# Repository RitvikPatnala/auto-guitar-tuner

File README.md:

# Auto Guitar Tuner

A handheld device that detects a guitar string's pitch and physically rotates the tuning peg until the string is in tune. Built around a custom ESP32-S3 PCB designed from schematic capture to routed layout, with real-time pitch detection firmware and closed-loop servo control. Tunes to within ±12 cents across all six strings and multiple tuning standards (Standard, Eb, Drop D, Open G).

## How it works?

1. A piezo vibration sensor mounted on the guitar picks up string vibrations (immune to ambient room noise, unlike a microphone).
2. An LM386 amplifier stage (gain ≈ 50) with a 1.6 kHz RC anti-aliasing filter conditions the signal for the ESP32-S3's ADC (8192 Hz, 12-bit).
3. Firmware detects the fundamental frequency using time-domain autocorrelation and computes the error from the target pitch in cents.
4. A PID controller drives an HS-318 servo attached to the tuning peg, making small angular corrections until the string is in tune — with safety interlocks (rotation limits, stall           detection, voicing threshold) to protect the guitar.
5. A TFT LCD (SPI) and two-button interface let the user select strings and tuning modes via an FSM-driven UI.

## Why Autocorrelation instaead of FFT?

The most interesting design decision in the project. Guitar strings produce strong harmonics — the 2nd harmonic often carries more energy than the fundamental, so naive FFT peak-picking frequently reports the octave above the true pitch. Time-domain autocorrelation measures the signal's self-similarity across lag values, which naturally locks onto the fundamental period. It was also faster on the ESP32-S3:

| Approach | Latency |
|---|---|
| Autocorrelation | ~22 ms |
| FFT + peak detection | ~48 ms |

The pipeline: Hann window → autocorrelation over the guitar's lag range (73–330 Hz) → normalization → zero-crossing peak detection → parabolic sub-sample interpolation for resolution beyond the lag grid. The ~22 ms loop lets the tuner track pitch continuously while the motor turns, so the user doesn't need to re-pluck after every adjustment.

## Hardware Design

- Power: dual AP62150 buck converters (9V battery → 5V and 3.3V rails). Chosen over LDOs after a dissipation analysis — a stalled servo draws 800 mA, which would burn 3.2 W in an LDO vs ~90% buck efficiency.
- Custom PCB: designed in KiCAD (schematic → layout), simulated in LTSpice; noise mitigated with ground partitioning, supply decoupling, and the RC input filter.

- Motor: HS-318 analog servo, selected over a stepper for closed-loop position feedback and full torque at low speed. Torque analysis: 0.25 kg·cm required at the peg vs 3.7 kg·cm available.

## Verification Highlights

| Subsystem | Result |
|---|---|
| Power rails | 3.353 V / 4.995 V measured (±1% of nominal) |
| Audio chain | Gain of ~52 measured (target 50); piezo signal 84 mV |
| Pitch detection | ±12 cents final tuning accuracy, ~22 ms latency |
| Control | Autonomous tuning verified on all 6 strings + alternate tunings |

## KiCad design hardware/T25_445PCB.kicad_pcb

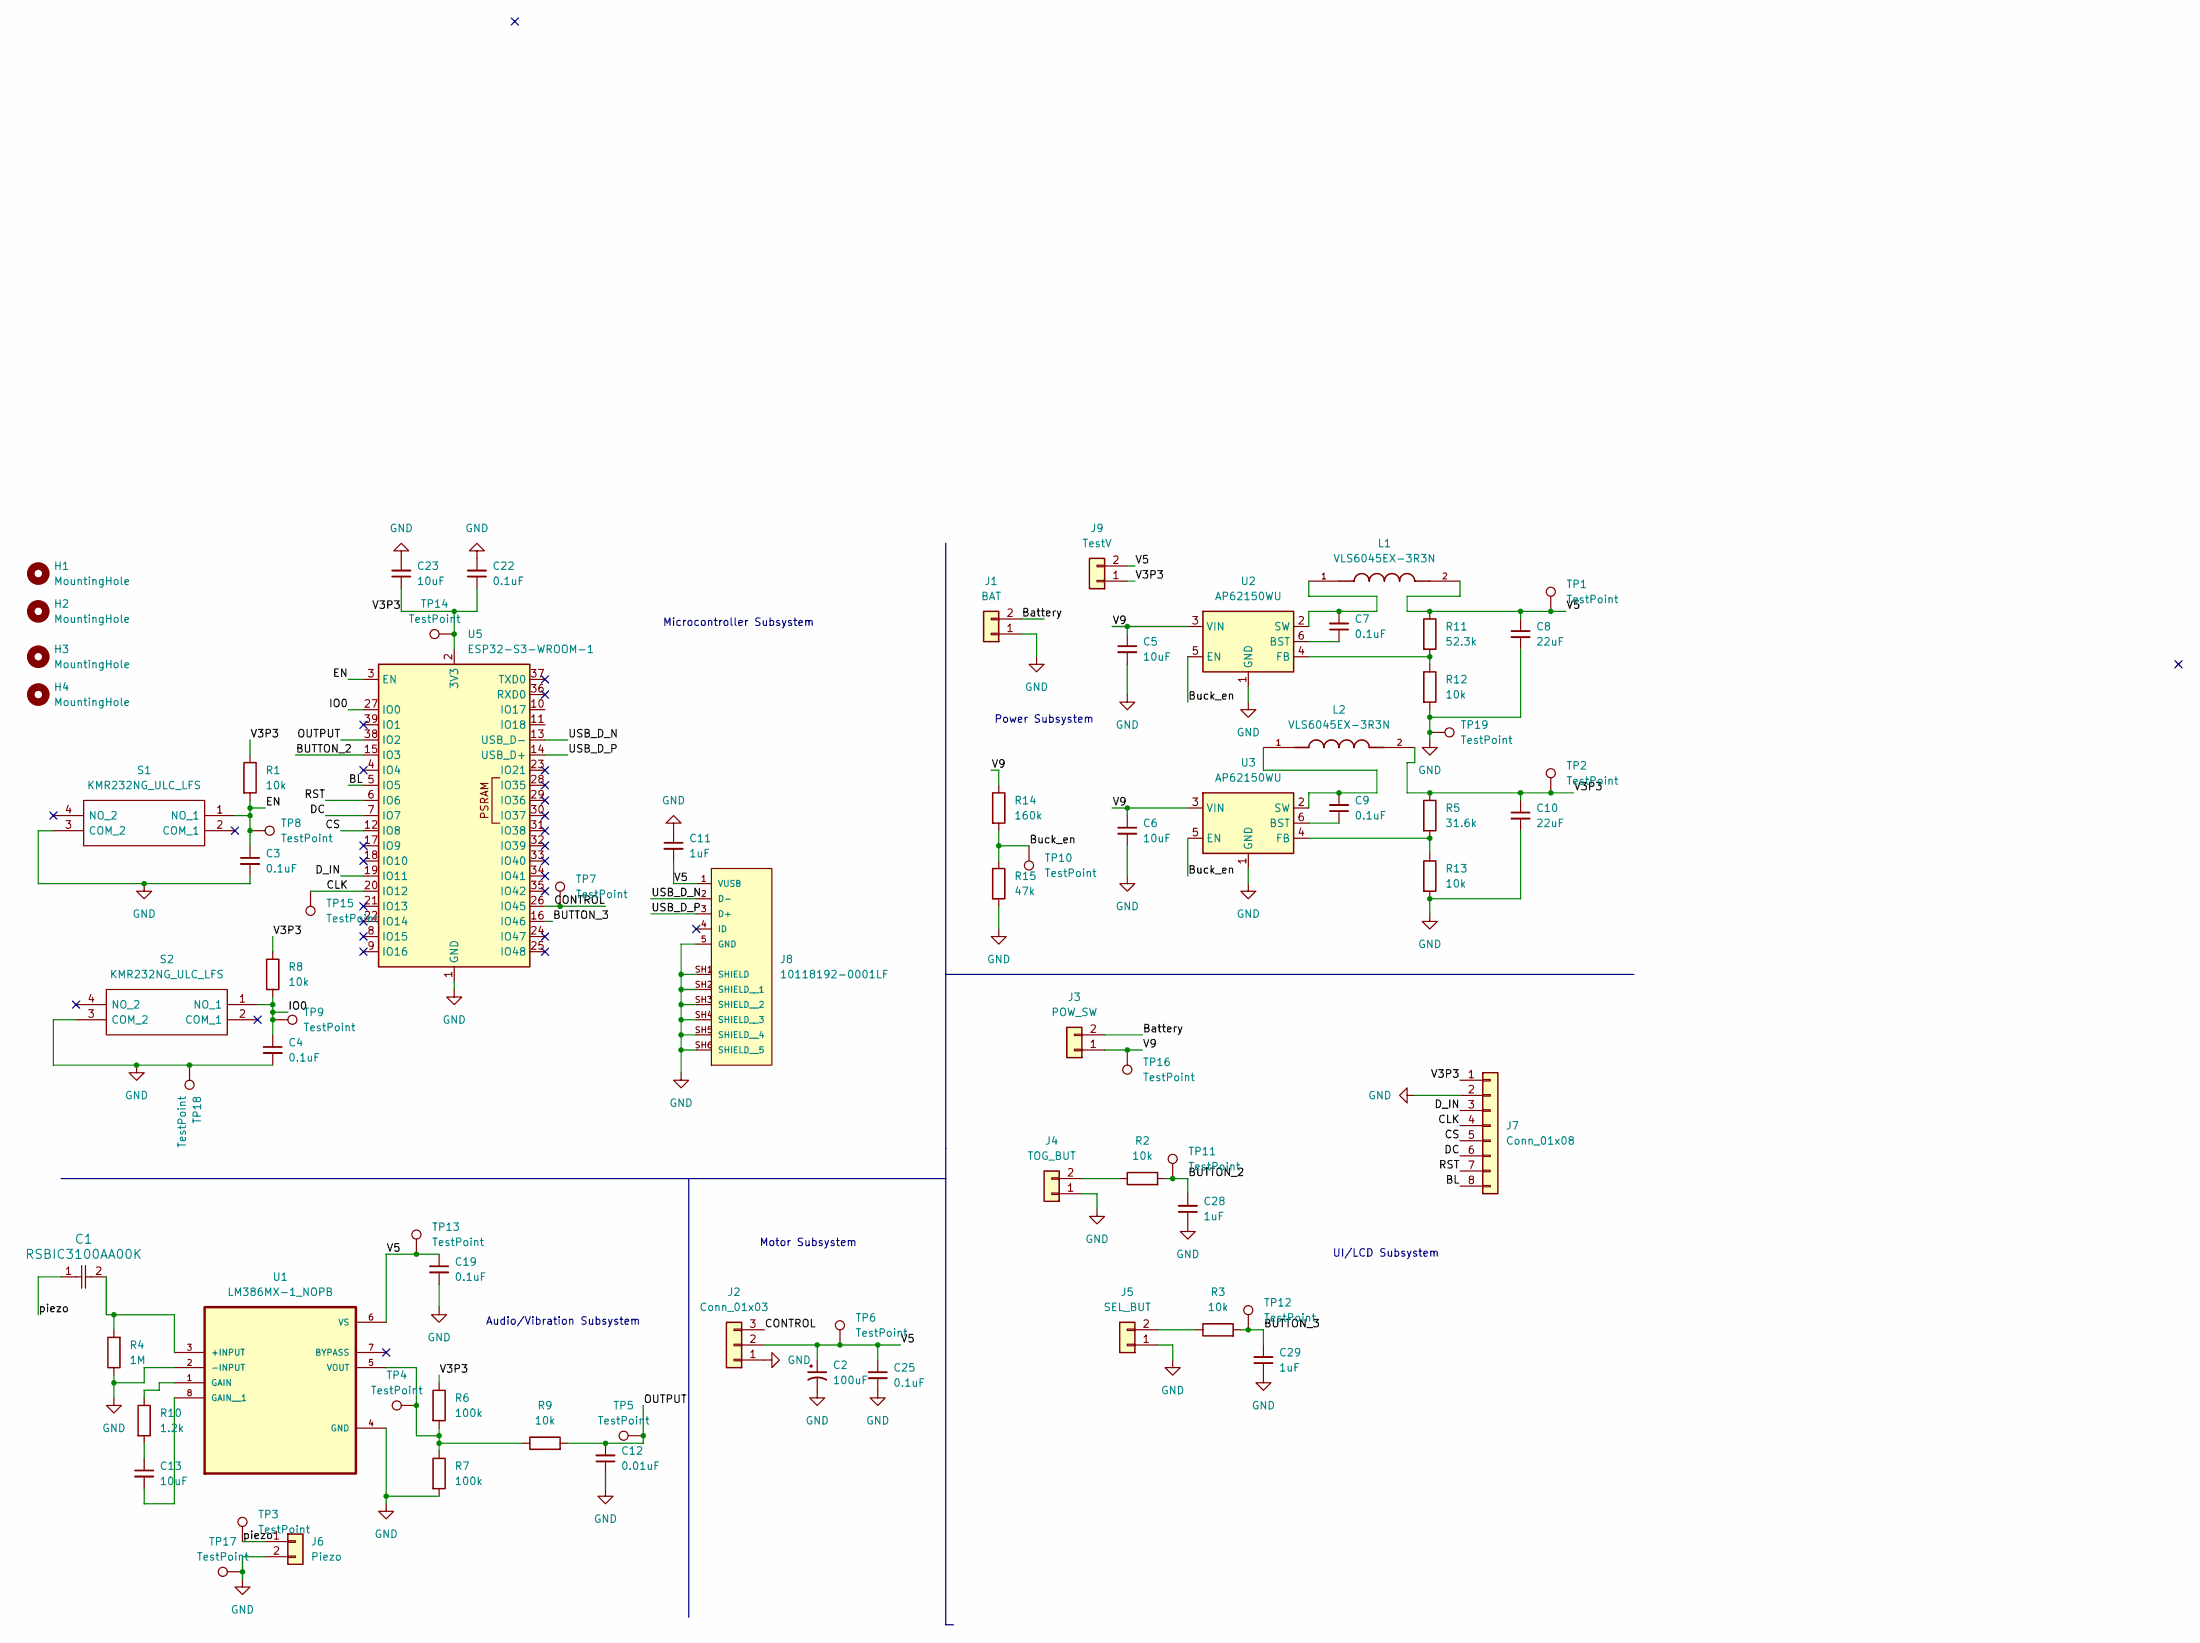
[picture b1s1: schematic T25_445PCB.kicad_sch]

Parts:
C1: RSBIC3100AA00K; CAP_RSBIC3100AA00K_KEM
C2: 100uF; CP_Radial_D6.3mm_P2.50mm
C3, C4, C7, C9, C19, C22, C25: 0.1uF; C_0805_2012Metric_Pad1.18x1.45mm_HandSolder
C5, C6, C13, C23: 10uF; C_0805_2012Metric_Pad1.18x1.45mm_HandSolder
C8, C10: 22uF; C_0805_2012Metric_Pad1.18x1.45mm_HandSolder
C11, C28, C29: 1uF; C_0805_2012Metric_Pad1.18x1.45mm_HandSolder
C12: 0.01uF; C_0805_2012Metric_Pad1.18x1.45mm_HandSolder
H1, H2, H3, H4: MountingHole; MountingHole_3.2mm_M3
J1: BAT; Molex_KK-254_AE-6410-02A_1x02_P2.54mm_Vertical
J2: Conn_01x03; Molex_KK-254_AE-6410-03A_1x03_P2.54mm_Vertical
J3: POW_SW; Molex_KK-254_AE-6410-02A_1x02_P2.54mm_Vertical
J4: TOG_BUT; Molex_KK-254_AE-6410-02A_1x02_P2.54mm_Vertical
J5: SEL_BUT; Molex_KK-254_AE-6410-02A_1x02_P2.54mm_Vertical
J6: Piezo; Molex_KK-254_AE-6410-02A_1x02_P2.54mm_Vertical
J7: Conn_01x08; Molex_KK-254_AE-6410-08A_1x08_P2.54mm_Vertical
J8: 10118192-0001LF; AMPHENOL_10118192-0001LF
J9: TestV; Molex_KK-254_AE-6410-02A_1x02_P2.54mm_Vertical
L1, L2: VLS6045EX-3R3N; IND_VLS6045EX-3R3N
R1, R2, R3, R8, R9, R12, R13: 10k; R_0805_2012Metric_Pad1.20x1.40mm_HandSolder
R4: 1M; R_0805_2012Metric_Pad1.20x1.40mm_HandSolder
R5: 31.6k; R_0805_2012Metric_Pad1.20x1.40mm_HandSolder
R6, R7: 100k; R_0805_2012Metric_Pad1.20x1.40mm_HandSolder
R10: 1.2k; R_0805_2012Metric_Pad1.20x1.40mm_HandSolder
R11: 52.3k; R_0805_2012Metric_Pad1.20x1.40mm_HandSolder
R14: 160k; R_0805_2012Metric_Pad1.20x1.40mm_HandSolder
R15: 47k; R_0805_2012Metric_Pad1.20x1.40mm_HandSolder
S1, S2: KMR232NG_ULC_LFS; KMR232NGULCLFS
TP1, TP2, TP6, TP13, TP14, TP16: TestPoint; TestPoint_Pad_D1.5mm
TP3, TP4, TP5, TP7, TP8, TP9, TP10, TP11, TP12, TP15: TestPoint; TestPoint_Pad_D1.0mm
TP17, TP18, TP19: TestPoint; TestPoint_Pad_D2.0mm
U1: LM386MX-1_NOPB; SOIC127P599X175-8N
U2, U3: AP62150WU; TSOT-23-6
U5: ESP32-S3-WROOM-1

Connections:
/BL: J7.8, U5.5 (IO5)
/BUTTON_2: C28.2, R2.2, TP11.1, U5.15 (IO3)
/BUTTON_3: C29.2, R3.2, TP12.1, U5.16 (IO46)
/Battery: J1.2, J3.2
/Buck_en: R14.2, R15.1, TP10.1, U2.5 (EN), U3.5 (EN)
/CLK: J7.4, TP15.1, U5.20 (IO12)
/CONTROL: J2.3, TP7.1, U5.26 (IO45)
/CS: J7.5, U5.12 (IO8)
/DC: J7.6, U5.7 (IO7)
/D_IN: J7.3, U5.19 (IO11)
/EN: C3.1, R1.2, S1.1 (NO_1), TP8.1, U5.3 (EN)
/IO0: C4.1, R8.2, S2.1 (NO_1), TP9.1, U5.27 (IO0)
/OUTPUT: C12.2, R9.2, TP5.1, U5.38 (IO2)
/RST: J7.7, U5.6 (IO6)
/USB_D_N: J8.2 (D-), U5.13 (USB_D-)
/USB_D_P: J8.3 (D+), U5.14 (USB_D+)
/V3P3: C10.1, C22.1, C23.1, J7.1, J9.1, L2.2, R1.1, R5.1, R6.1, R8.1, TP2.1, TP14.1, U5.2 (3V3)
/V5: C2.1, C8.1, C11.2, C19.1, C25.1, J2.2, J8.1 (VUSB), J9.2, L1.2, R11.1, TP1.1, TP6.1, TP13.1, U1.6 (VS)
/V9: C5.1, C6.1, J3.1, R14.1, TP16.1, U2.3 (VIN), U3.3 (VIN)
/piezo: C1.1, J6.1, TP3.1
GND: C2.2, C3.2, C4.2, C5.2, C6.2, C8.2, C10.2, C11.1, C12.1, C19.2, C22.2, C23.2, C25.2, C28.1, C29.1, J1.1, J2.1, J4.1, J5.1, J6.2, J7.2, J8.5 (GND), J8.SH1 (SHIELD), J8.SH2 (SHIELD__1), J8.SH3 (SHIELD__2), J8.SH4 (SHIELD__3), J8.SH5 (SHIELD__4), J8.SH6 (SHIELD__5), R4.1, R7.2, R12.2, R13.2, R15.2, S1.3 (COM_2), S2.3 (COM_2), TP17.1, TP18.1, TP19.1, U1.2 (-INPUT), U1.4 (GND), U2.1 (GND), U3.1 (GND), U5.1 (GND), U5.40 (GND), U5.41 (GND)
unnamed: C13.1, R10.2
unnamed: J4.2, R2.1
unnamed: J5.2, R3.1
unnamed: C1.2, R4.2, U1.3 (+INPUT)
unnamed: R10.1, U1.1 (GAIN)
unnamed: C13.2, U1.8 (GAIN__1)
unnamed: R6.2, R7.1, R9.1, TP4.1, U1.5 (VOUT)
unnamed: C7.1, U2.6 (BST)
unnamed: R11.2, R12.1, U2.4 (FB)
unnamed: C7.2, L1.1, U2.2 (SW)
unnamed: C9.1, U3.6 (BST)
unnamed: R5.2, R13.1, U3.4 (FB)
unnamed: C9.2, L2.1, U3.2 (SW)

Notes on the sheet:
Power Subsystem
Audio/Vibration Subsystem
Microcontroller Subsystem
UI/LCD Subsystem
Motor Subsystem

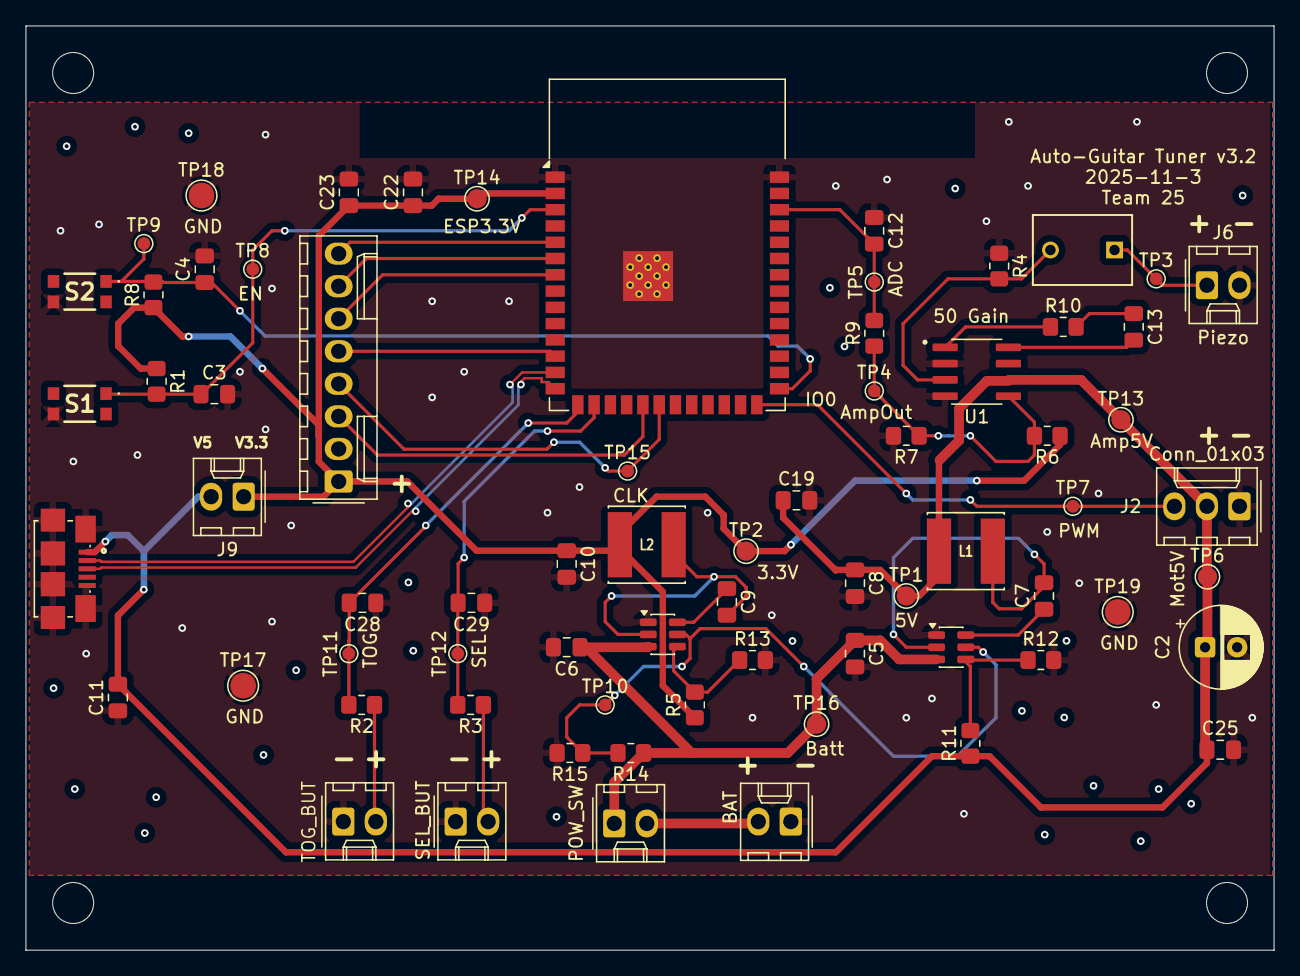
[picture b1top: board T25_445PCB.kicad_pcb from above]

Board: 2 copper layers, 97.4 x 72.1 mm, 74 parts (0 on the bottom side), 34 nets.
